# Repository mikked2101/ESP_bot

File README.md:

# ESP_bot
A single-circuit board robot

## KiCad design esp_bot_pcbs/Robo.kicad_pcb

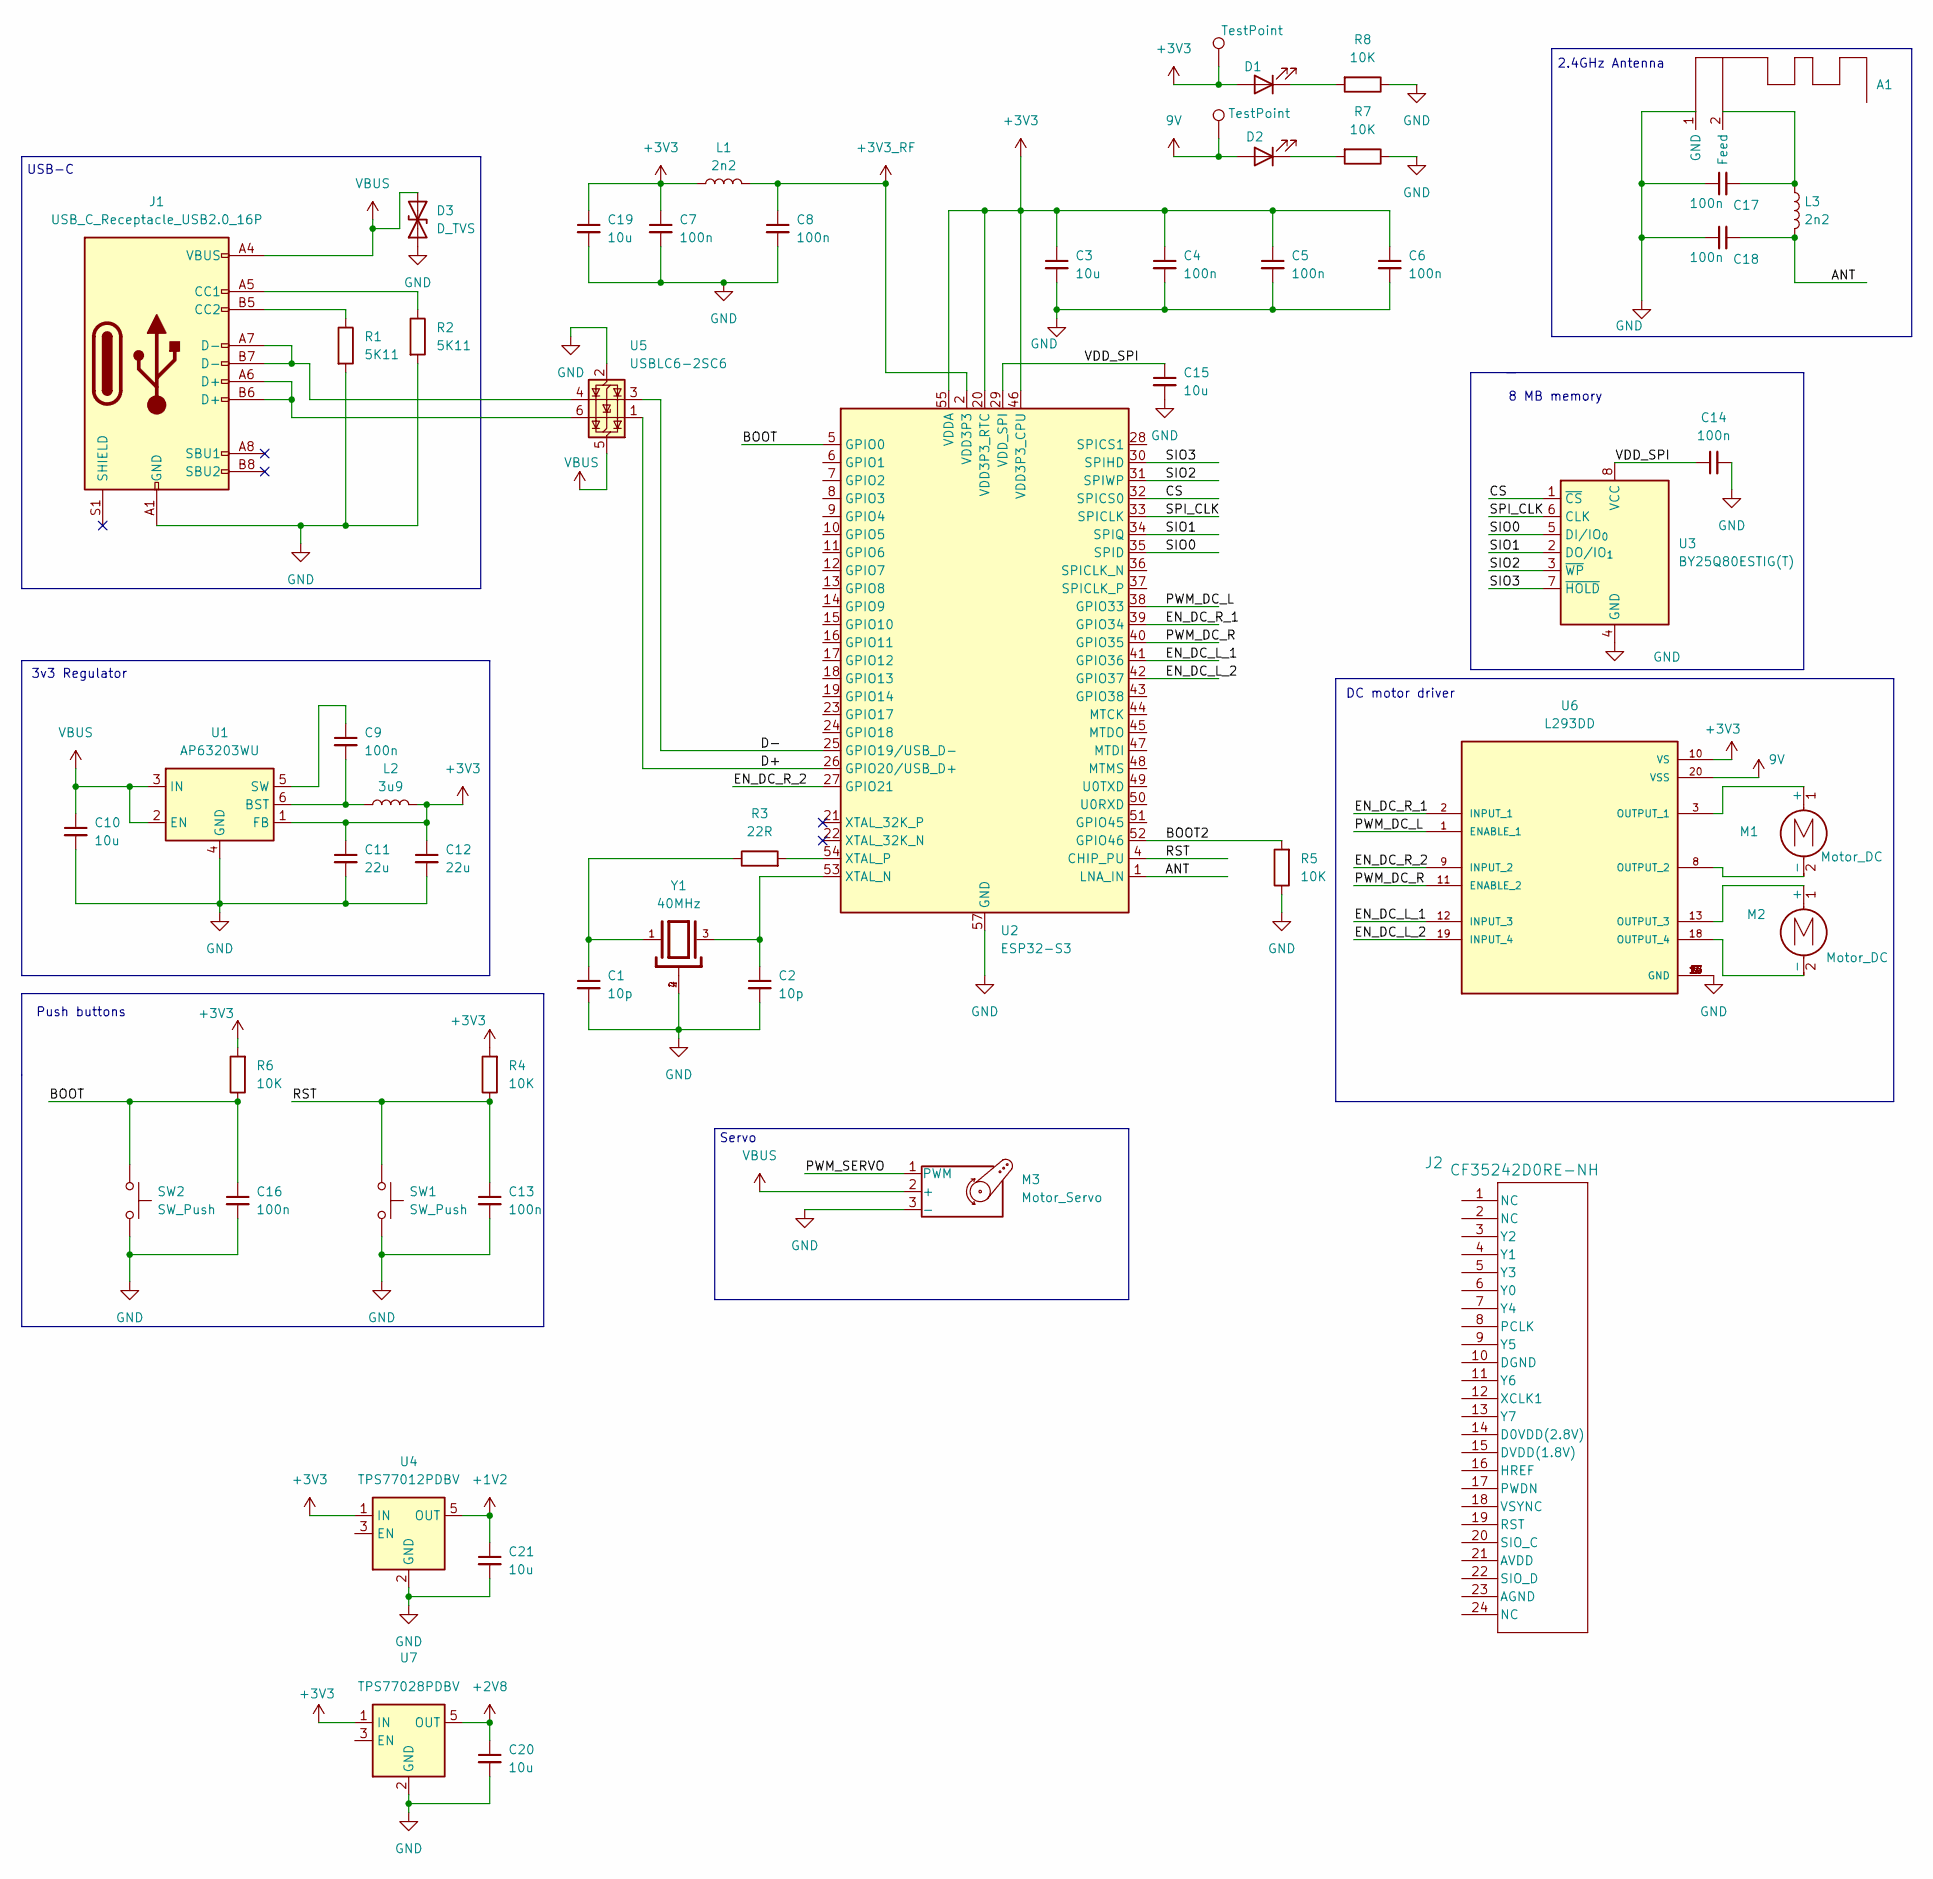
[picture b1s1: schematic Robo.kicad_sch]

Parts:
A1: PCB_Wifi_Antenna
C1, C2: 10p; C_0805_2012Metric_Pad1.18x1.45mm_HandSolder
C3, C10, C15, C19, C20, C21: 10u; C_0805_2012Metric_Pad1.18x1.45mm_HandSolder
C4, C5, C6, C7, C8, C9, C13, C14, C16, C17, C18: 100n; C_0805_2012Metric_Pad1.18x1.45mm_HandSolder
C11, C12: 22u; C_0805_2012Metric_Pad1.18x1.45mm_HandSolder
D1, D2: LED; LED_0805_2012Metric_Pad1.15x1.40mm_HandSolder
D3: D_TVS; D_0805_2012Metric_Pad1.15x1.40mm_HandSolder
J1: USB_C_Receptacle_USB2.0_16P; USB_C_Receptacle_GCT_USB4105-xx-A_16P_TopMnt_Horizontal
J2: CF35242D0RE-NH; CONN24X1_CF35242D0RE-NH_CVI
L1, L3: 2n2; L_0805_2012Metric_Pad1.15x1.40mm_HandSolder
L2: 3u9; L_0805_2012Metric_Pad1.15x1.40mm_HandSolder
M1, M2: Motor_DC; PinHeader_1x02_P2.54mm_Vertical
M3: Motor_Servo; PinHeader_1x03_P2.54mm_Vertical
R1, R2: 5K11; R_0805_2012Metric_Pad1.20x1.40mm_HandSolder
R3: 22R; R_0805_2012Metric_Pad1.20x1.40mm_HandSolder
R4, R5, R6, R7, R8: 10K; R_0805_2012Metric_Pad1.20x1.40mm_HandSolder
SW1, SW2: SW_Push; SW_Push_1P1T_NO_E-Switch_TL3301NxxxxxG
TP1, TP2: TestPoint
U1: AP63203WU; TSOT-23-6
U2: ESP32-S3; QFN-56-1EP_7x7mm_P0.4mm_EP4x4mm_ThermalVias
U3: BY25Q80ESTIG(T); JEITA_SOIC-8_3.9x4.9mm_P1.27mm
U4: TPS77012PDBV; SOT-23-5_HandSoldering
U5: USBLC6-2SC6; SOT-23-6_Handsoldering
U6: L293DD; SOIC127P1032X265-20N; PARTREV N/A
U7: TPS77028PDBV; SOT-23-5_HandSoldering
Y1: 40MHz; XTAL_ECS-400-10-37B2-CKM-TR; PARTREV 2021

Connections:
9V: D2.2 (A), TP2.1, U6.20 (VSS)
+1V2: C21.1, U4.5 (OUT)
+2V8: C20.1, U7.5 (OUT)
+3V3: C3.1, C4.1, C5.1, C6.1, C7.1, C11.1, C12.1, C19.1, D1.2 (A), L1.1, L2.2, R4.2, R6.2, TP1.1, U1.1 (FB), U2.20 (VDD3P3_RTC), U2.46 (VDD3P3_CPU), U2.55 (VDDA), U2.56 (VDDA), U4.1 (IN), U6.10 (VS), U7.1 (IN)
+3V3_RF: C8.1, L1.2, U2.2 (VDD3P3), U2.3 (VDD3P3)
/ANT: C18.2, L3.2, U2.1 (LNA_IN)
/BOOT: C16.1, R6.1, SW2.1, U2.5 (GPIO0)
/BOOT2: R5.2, U2.52 (GPIO46)
/CS: U2.32 (SPICS0), U3.1 (~CS)
/D+: U2.26 (GPIO20/USB_D+), U5.1 (I/O1)
/D-: U2.25 (GPIO19/USB_D-), U5.3 (I/O2)
/EN_DC_L_1: U2.41 (GPIO36), U6.12 (INPUT_3)
/EN_DC_L_2: U2.42 (GPIO37), U6.19 (INPUT_4)
/EN_DC_R_1: U2.39 (GPIO34), U6.2 (INPUT_1)
/EN_DC_R_2: U2.27 (GPIO21), U6.9 (INPUT_2)
/PWM_DC_L: U2.38 (GPIO33), U6.1 (ENABLE_1)
/PWM_DC_R: U2.40 (GPIO35), U6.11 (ENABLE_2)
/PWM_SERVO: M3.1 (PWM)
/RST: C13.1, R4.1, SW1.1, U2.4 (CHIP_PU)
/SIO0: U2.35 (SPID), U3.5 (DI/IO_{0})
/SIO1: U2.34 (SPIQ), U3.2 (DO/IO_{1})
/SIO2: U2.31 (SPIWP), U3.3 (~WP)
/SIO3: U2.30 (SPIHD), U3.7 (~HOLD)
/SPI_CLK: U2.33 (SPICLK), U3.6 (CLK)
/VDD_SPI: C14.1, C15.1, U2.29 (VDD_SPI), U3.8 (VCC)
GND: A1.1 (GND), C1.2, C2.2, C3.2, C4.2, C5.2, C6.2, C7.2, C8.2, C10.2, C11.2, C12.2, C13.2, C14.2, C15.2, C16.2, C17.1, C18.1, C19.2, C20.2, C21.2, D3.1 (A1), J1.A1 (GND), J1.A12 (GND), J1.B1 (GND), J1.B12 (GND), M3.3 (-), R1.2, R2.2, R5.1, R7.1, R8.1, SW1.2, SW2.2, U1.4 (GND), U2.57 (GND), U3.4 (GND), U4.2 (GND), U4.4 (GND), U5.2 (GND), U6.4 (GND), U6.5 (GND), U6.6 (GND), U6.7 (GND), U6.14 (GND), U6.15 (GND), U6.16 (GND), U6.17 (GND), U7.2 (GND), U7.4 (GND), Y1.2, Y1.4
unnamed: A1.2 (Feed), C17.2, L3.1
unnamed: C1.1, R3.1, Y1.1
unnamed: D1.1 (K), R8.2
unnamed: D2.1 (K), R7.2
unnamed: J1.A5 (CC1), R2.1
unnamed: J1.B5 (CC2), R1.1
unnamed: J1.A6 (D+), J1.B6 (D+), U5.6 (I/O1)
unnamed: J1.A7 (D-), J1.B7 (D-), U5.4 (I/O2)
unnamed: M1.1 (+), U6.3 (OUTPUT_1)
unnamed: M1.2 (-), U6.8 (OUTPUT_2)
unnamed: M2.1 (+), U6.13 (OUTPUT_3)
unnamed: M2.2 (-), U6.18 (OUTPUT_4)
unnamed: C9.2, L2.1, U1.6 (BST)
unnamed: C9.1, U1.5 (SW)
unnamed: C2.1, U2.53 (XTAL_N), Y1.3
unnamed: R3.2, U2.54 (XTAL_P)
VBUS: C10.1, D3.2 (A2), J1.A4 (VBUS), J1.A9 (VBUS), J1.B4 (VBUS), J1.B9 (VBUS), M3.2 (+), U1.2 (EN), U1.3 (IN), U5.5 (VBUS)

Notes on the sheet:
Servo
Push buttons
USB-C
2.4GHz Antenna
DC motor driver
3v3 Regulator
8 MB memory

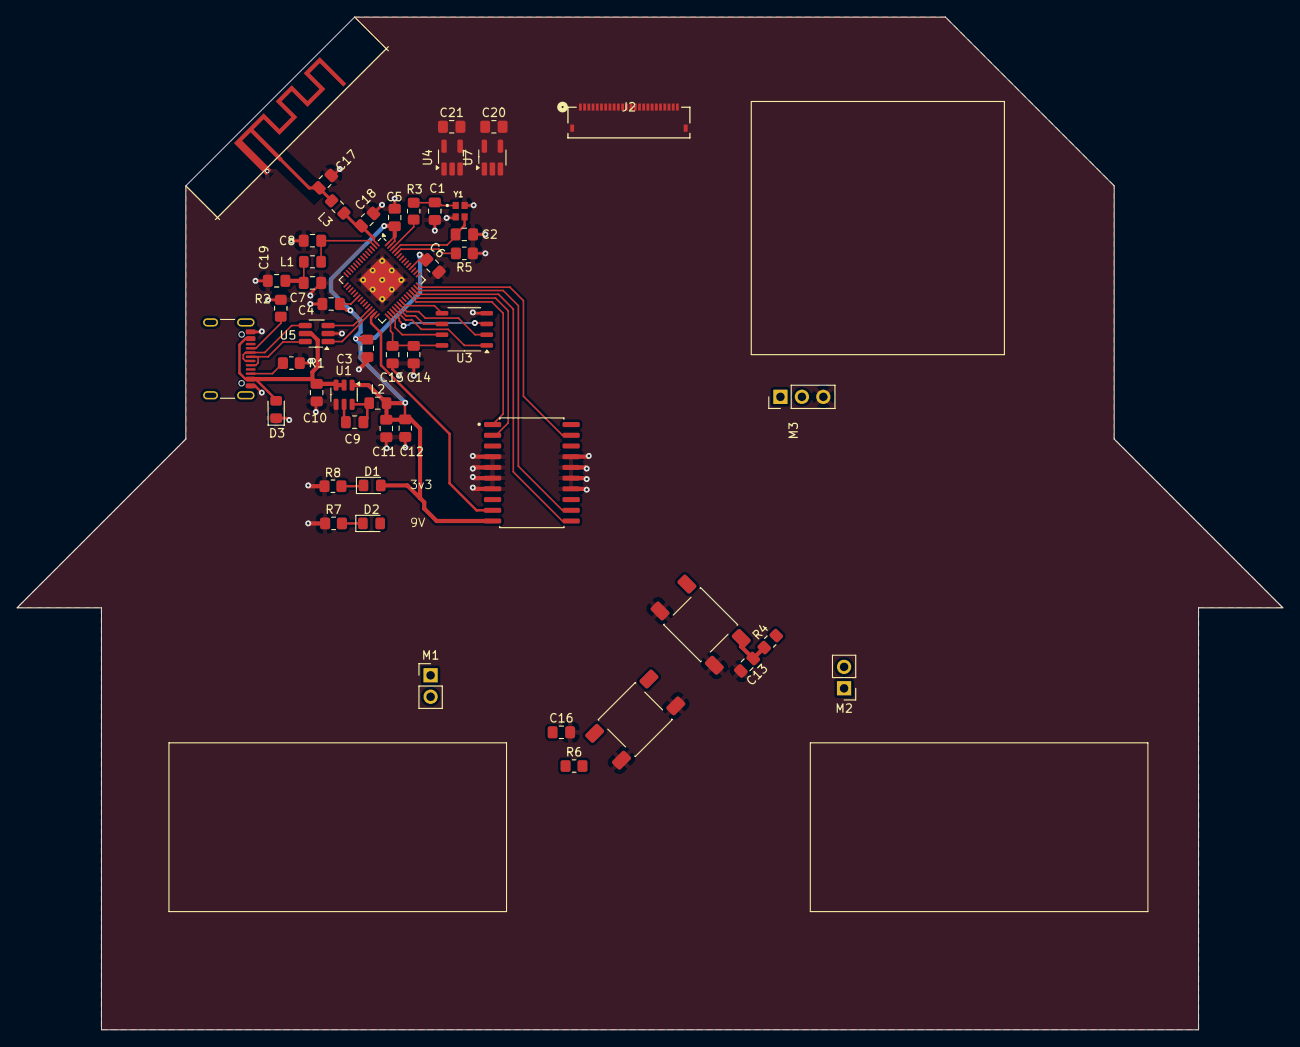
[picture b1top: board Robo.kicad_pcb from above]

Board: 4 copper layers, 150.0 x 120.0 mm, 51 parts (0 on the bottom side), 42 nets.

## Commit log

2025-08-20 changed folder structure
